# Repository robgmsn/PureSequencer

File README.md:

DESIGN STATUS: Production

Sequencer Updated to V2.31 28/4/21

Power Supply updated pull 5V from main case power supply, in line with low noise techniques.
Some resistor values reduced to 10k, in line with low noise techniques.
Traces rerouted.

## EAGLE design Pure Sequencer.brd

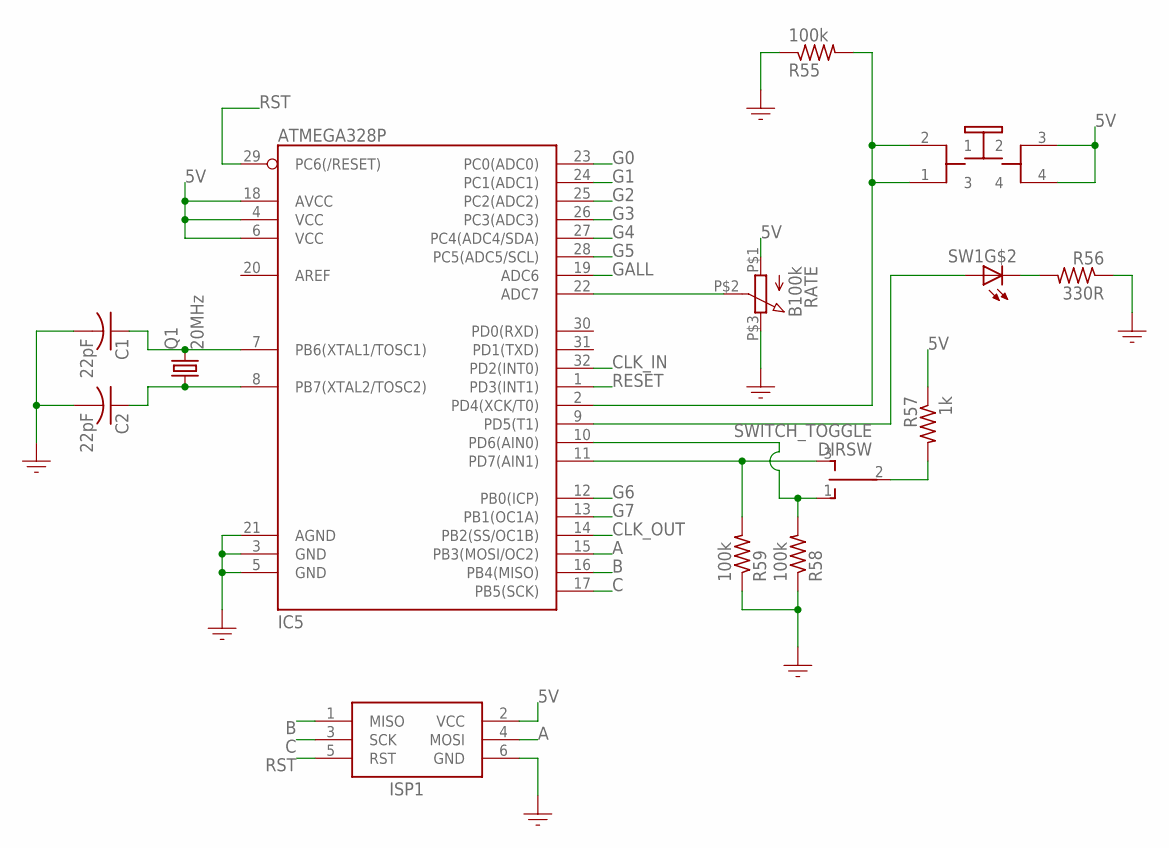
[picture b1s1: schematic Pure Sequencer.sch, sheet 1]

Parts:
C1, C2: 22pF; C0805
DIRSW: SWITCH_TOGGLE; TOGGLE_SW
IC5: ATMEGA328P; TQFP32-08
ISP1: HEADER2X3-6; AVRISP
Q1: 20MHz; HC49UP
R55, R58, R59: 100k; R0805
R56: 330R; R0805
R57: 1k; R0805
RATE: B100k; POTENTIOMETER_9MM
SW1: SWITCH_PUSHBUTTON_LED; PB6149L

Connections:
5V: IC5.4 (VCC), IC5.6 (VCC), IC5.18 (AVCC), ISP1.2 (VCC), R57.1, RATE.P$1 (1), SW1.3 (2), SW1.4; also elsewhere on the board
A: IC5.15 (PB3(MOSI/OC2)), ISP1.4 (MOSI); also elsewhere on the board
B: IC5.16 (PB4(MISO)), ISP1.1 (MISO); also elsewhere on the board
C: IC5.17 (PB5(SCK)), ISP1.3 (SCK); also elsewhere on the board
CLK_IN: IC5.32 (PD2(INT0)); also elsewhere on the board
CLK_OUT: IC5.14 (PB2(SS/OC1B)); also elsewhere on the board
G0: IC5.23 (PC0(ADC0)); also elsewhere on the board
G1: IC5.24 (PC1(ADC1)); also elsewhere on the board
G2: IC5.25 (PC2(ADC2)); also elsewhere on the board
G3: IC5.26 (PC3(ADC3)); also elsewhere on the board
G4: IC5.27 (PC4(ADC4/SDA)); also elsewhere on the board
G5: IC5.28 (PC5(ADC5/SCL)); also elsewhere on the board
G6: IC5.12 (PB0(ICP)); also elsewhere on the board
G7: IC5.13 (PB1(OC1A)); also elsewhere on the board
GALL: IC5.19 (ADC6)
GND: C1.2, C2.2, IC5.3 (GND), IC5.5 (GND), IC5.21 (AGND), ISP1.6 (GND), R55.1, R56.1, R58.1, R59.1, RATE.P$3 (3); also elsewhere on the board
unnamed: C1.1, IC5.7 (PB6(XTAL1/TOSC1)), Q1.2
unnamed: C2.1, IC5.8 (PB7(XTAL2/TOSC2)), Q1.1
unnamed: IC5.22 (ADC7), RATE.P$2 (2)
unnamed: IC5.2 (PD4(XCK/T0)), R55.2, SW1.1 (3), SW1.2 (1)
unnamed: IC5.9 (PD5(T1)), SW1.A
unnamed: R56.2, SW1.K (C)
unnamed: DIRSW.2, R57.2
unnamed: DIRSW.1 (O), IC5.10 (PD6(AIN0)), R58.2
unnamed: DIRSW.3 (S), IC5.11 (PD7(AIN1)), R59.2
RESET: IC5.1 (PD3(INT1)); also elsewhere on the board
RST: IC5.29 (PC6(/RESET)), ISP1.5 (RST)

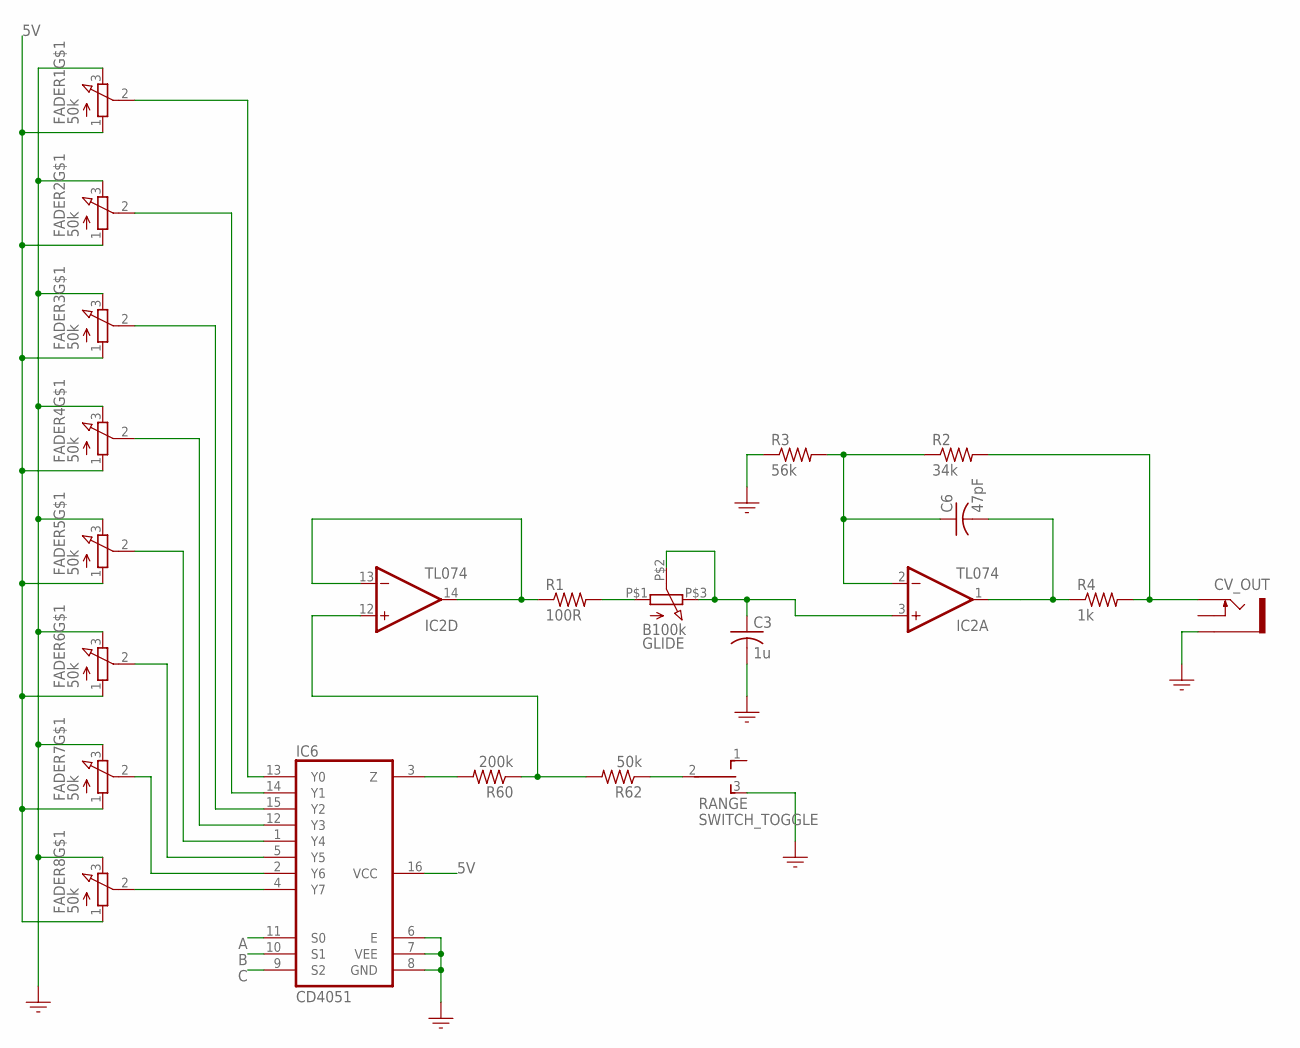
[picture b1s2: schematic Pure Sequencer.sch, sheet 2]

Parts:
C3: 1u; C0805
C6: 47pF; C0805
CV_OUT: PJ301M-12
FADER1, FADER2, FADER3, FADER4, FADER5, FADER6, FADER7, FADER8: 50k; FADER_20MM_LED
GLIDE: B100k; POTENTIOMETER_9MM
IC2: TL074; SO14
IC6: CD4051; SOIC_16
R1: 100R; R0805
R2: 34k; R0805
R3: 56k; R0805
R4: 1k; R0805
R60: 200k; R0805
R62: 50k; R0805
RANGE: SWITCH_TOGGLE; TOGGLE_SW

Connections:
5V: FADER1.1, FADER2.1, FADER3.1, FADER4.1, FADER5.1, FADER6.1, FADER7.1, FADER8.1, IC6.16 (VCC); also elsewhere on the board
A: IC6.11 (S0); also elsewhere on the board
B: IC6.10 (S1); also elsewhere on the board
C: IC6.9 (S2); also elsewhere on the board
GND: C3.2, CV_OUT.GND (SLEEVE), FADER1.3, FADER2.3, FADER3.3, FADER4.3, FADER5.3, FADER6.3, FADER7.3, FADER8.3, IC6.6 (E), IC6.7 (VEE), IC6.8 (GND), R3.1, RANGE.3 (S); also elsewhere on the board
unnamed: IC2.12 (+IN), R60.1, R62.2
unnamed: IC2.13 (-IN), IC2.14 (OUT), R1.1
unnamed: GLIDE.P$1 (1), R1.2
unnamed: FADER8.2, IC6.4 (Y7)
unnamed: FADER7.2, IC6.2 (Y6)
unnamed: FADER6.2, IC6.5 (Y5)
unnamed: FADER5.2, IC6.1 (Y4)
unnamed: FADER4.2, IC6.12 (Y3)
unnamed: FADER3.2, IC6.15 (Y2)
unnamed: FADER2.2, IC6.14 (Y1)
unnamed: FADER1.2, IC6.13 (Y0)
unnamed: C3.1, GLIDE.P$2 (2), GLIDE.P$3 (3), IC2.3 (+IN)
unnamed: C6.1, IC2.2 (-IN), R2.1, R3.2
unnamed: C6.2, IC2.1 (OUT), R4.1
unnamed: CV_OUT.TIP, R2.2, R4.2
unnamed: IC6.3 (Z), R60.2
unnamed: R62.1, RANGE.2

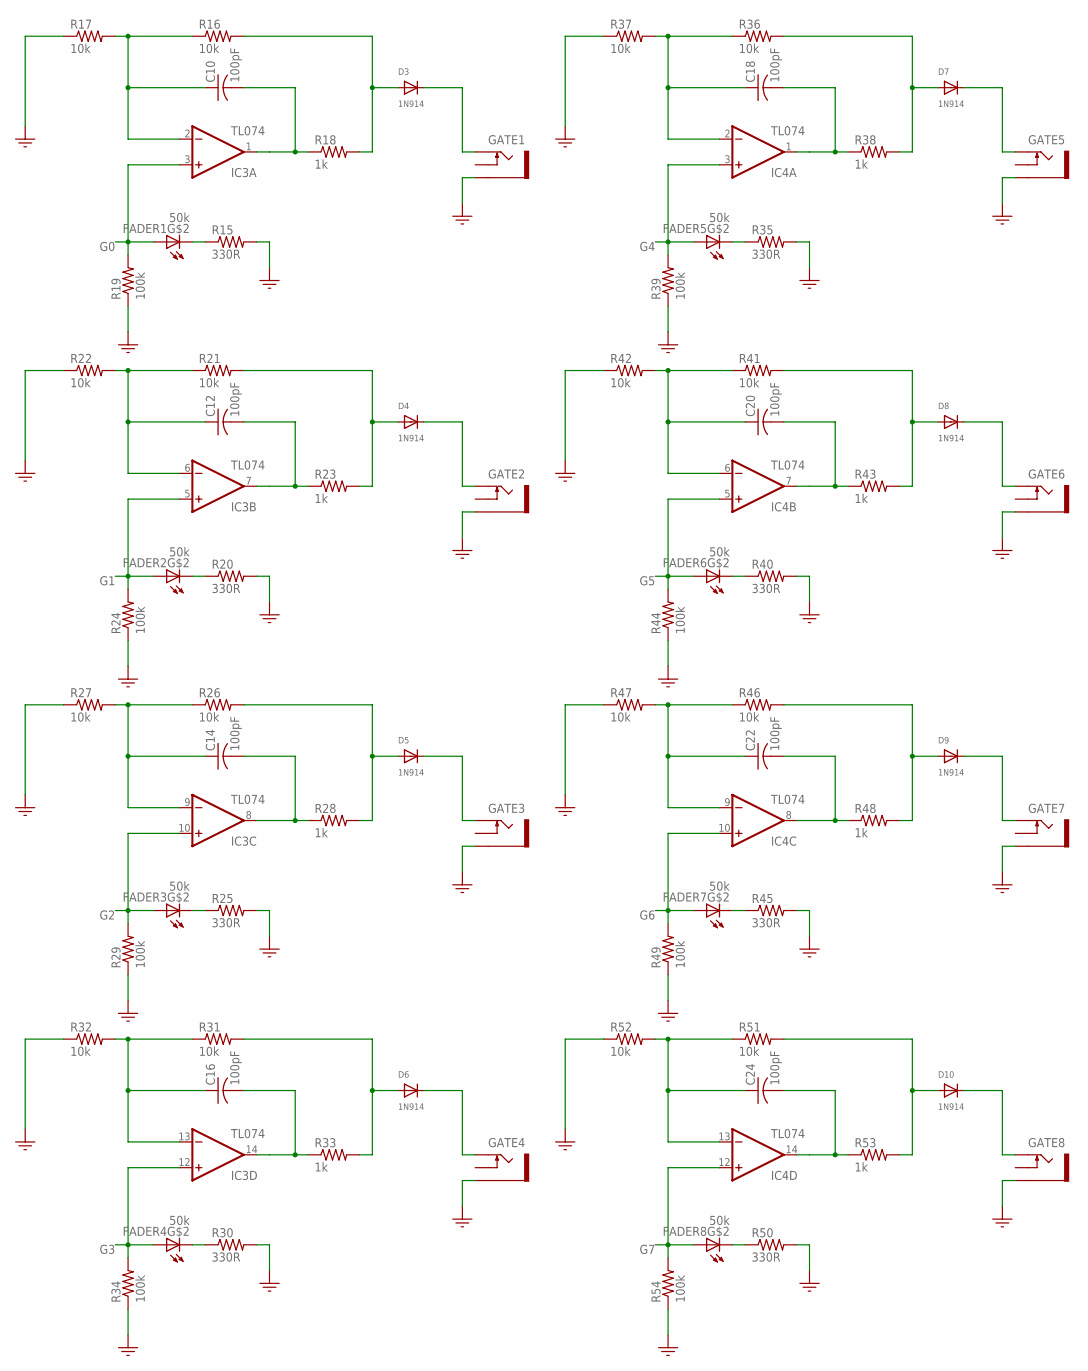
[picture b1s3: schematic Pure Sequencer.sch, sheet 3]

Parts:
C10, C12, C14, C16, C18, C20, C22, C24: 100pF; C0805
D3, D4, D5, D6, D7, D8, D9, D10: 1N914; DO-41
FADER1, FADER2, FADER3, FADER4, FADER5, FADER6, FADER7, FADER8: 50k; FADER_20MM_LED
GATE1, GATE2, GATE3, GATE4, GATE5, GATE6, GATE7, GATE8: PJ301M-12
IC3, IC4: TL074; SO14
R15, R20, R25, R30, R35, R40, R45, R50: 330R; R0805
R16, R17, R21, R22, R26, R27, R31, R32, R36, R37, R41, R42, R46, R47, R51, R52: 10k; R0805
R18, R23, R28, R33, R38, R43, R48, R53: 1k; R0805
R19, R24, R29, R34, R39, R44, R49, R54: 100k; R0805

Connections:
G0: FADER1.A, IC3.3 (+IN), R19.2; also elsewhere on the board
G1: FADER2.A, IC3.5 (+IN), R24.2; also elsewhere on the board
G2: FADER3.A, IC3.10 (+IN), R29.2; also elsewhere on the board
G3: FADER4.A, IC3.12 (+IN), R34.2; also elsewhere on the board
G4: FADER5.A, IC4.3 (+IN), R39.2; also elsewhere on the board
G5: FADER6.A, IC4.5 (+IN), R44.2; also elsewhere on the board
G6: FADER7.A, IC4.10 (+IN), R49.2; also elsewhere on the board
G7: FADER8.A, IC4.12 (+IN), R54.2; also elsewhere on the board
GND: GATE1.GND (SLEEVE), GATE2.GND (SLEEVE), GATE3.GND (SLEEVE), GATE4.GND (SLEEVE), GATE5.GND (SLEEVE), GATE6.GND (SLEEVE), GATE7.GND (SLEEVE), GATE8.GND (SLEEVE), R15.2, R17.1, R19.1, R20.2, R22.1, R24.1, R25.2, R27.1, R29.1, R30.2, R32.1, R34.1, R35.2, R37.1, R39.1, R40.2, R42.1, R44.1, R45.2, R47.1, R49.1, R50.2, R52.1, R54.1; also elsewhere on the board
unnamed: FADER1.K (C), R15.1
unnamed: C10.1, IC3.2 (-IN), R16.1, R17.2
unnamed: C10.2, IC3.1 (OUT), R18.1
unnamed: D3.A, R16.2, R18.2
unnamed: FADER3.K (C), R25.1
unnamed: FADER2.K (C), R20.1
unnamed: C12.1, IC3.6 (-IN), R21.1, R22.2
unnamed: C12.2, IC3.7 (OUT), R23.1
unnamed: D4.A, R21.2, R23.2
unnamed: C14.1, IC3.9 (-IN), R26.1, R27.2
unnamed: C14.2, IC3.8 (OUT), R28.1
unnamed: D5.A, R26.2, R28.2
unnamed: FADER4.K (C), R30.1
unnamed: C16.1, IC3.13 (-IN), R31.1, R32.2
unnamed: C16.2, IC3.14 (OUT), R33.1
unnamed: D6.A, R31.2, R33.2
unnamed: FADER5.K (C), R35.1
unnamed: C18.1, IC4.2 (-IN), R36.1, R37.2
unnamed: C18.2, IC4.1 (OUT), R38.1
unnamed: D7.A, R36.2, R38.2
unnamed: FADER6.K (C), R40.1
unnamed: C20.1, IC4.6 (-IN), R41.1, R42.2
unnamed: C20.2, IC4.7 (OUT), R43.1
unnamed: D8.A, R41.2, R43.2
unnamed: FADER7.K (C), R45.1
unnamed: C22.1, IC4.9 (-IN), R46.1, R47.2
unnamed: C22.2, IC4.8 (OUT), R48.1
unnamed: D9.A, R46.2, R48.2
unnamed: FADER8.K (C), R50.1
unnamed: C24.1, IC4.13 (-IN), R51.1, R52.2
unnamed: C24.2, IC4.14 (OUT), R53.1
unnamed: D10.A, R51.2, R53.2
unnamed: D6.C, GATE4.TIP
unnamed: D5.C, GATE3.TIP
unnamed: D4.C, GATE2.TIP
unnamed: D3.C, GATE1.TIP
unnamed: D10.C, GATE8.TIP
unnamed: D9.C, GATE7.TIP
unnamed: D8.C, GATE6.TIP
unnamed: D7.C, GATE5.TIP

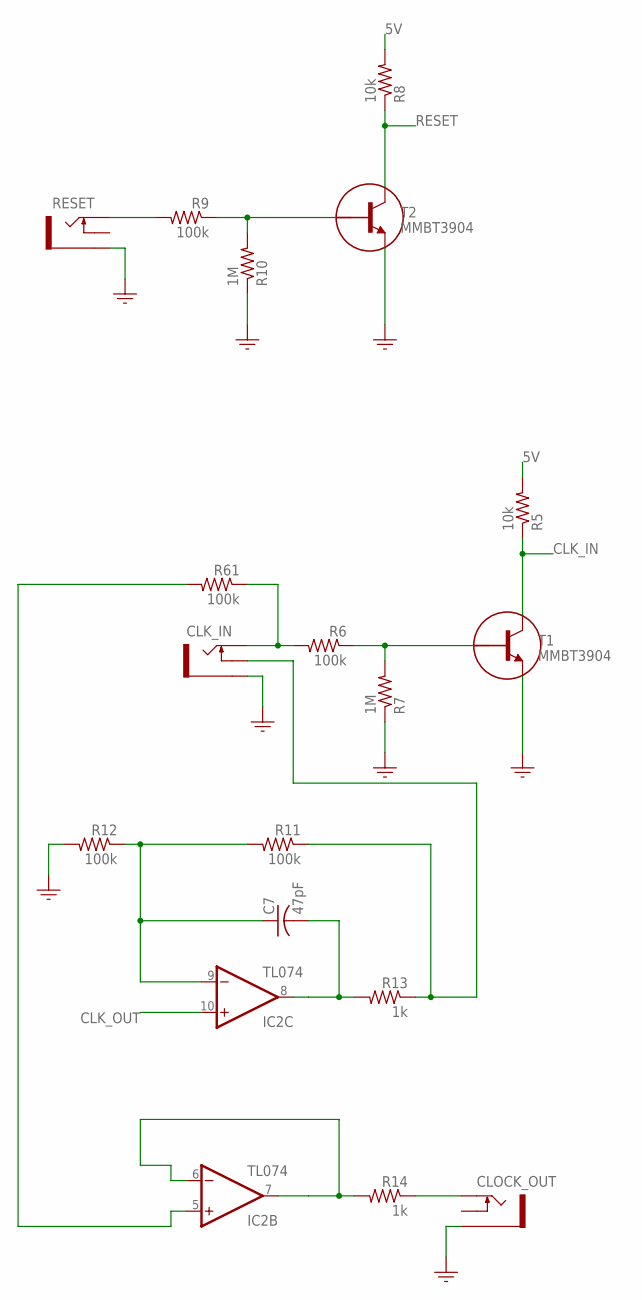
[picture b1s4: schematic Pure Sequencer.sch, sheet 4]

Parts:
C7: 47pF; C0805
CLK_IN: PJ301M-12
CLOCK_OUT: PJ301M-12
IC2: TL074; SO14
R5, R8: 10k; R0805
R6, R9, R11, R12, R61: 100k; R0805
R7, R10: 1M; R0805
R13, R14: 1k; R0805
RESET: PJ301M-12
T1, T2: MMBT3904; SOT23

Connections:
5V: R5.2, R8.2; also elsewhere on the board
CLK_IN: R5.1, T1.3 (C); also elsewhere on the board
CLK_OUT: IC2.10 (+IN); also elsewhere on the board
GND: CLK_IN.GND (SLEEVE), CLOCK_OUT.GND (SLEEVE), R7.1, R10.1, R12.2, RESET.GND (SLEEVE), T1.2 (E), T2.2 (E); also elsewhere on the board
unnamed: R6.1, R7.2, T1.1 (B)
unnamed: IC2.5 (+IN), R61.2
unnamed: R9.1, R10.2, T2.1 (B)
unnamed: R9.2, RESET.TIP
unnamed: C7.1, IC2.9 (-IN), R11.2, R12.1
unnamed: C7.2, IC2.8 (OUT), R13.2
unnamed: CLK_IN.TIP, R6.2, R61.1
unnamed: IC2.6 (-IN), IC2.7 (OUT), R14.2
unnamed: CLOCK_OUT.TIP, R14.1
unnamed: CLK_IN.NORM (SWITCH), R11.1, R13.1
RESET: R8.1, T2.3 (C); also elsewhere on the board

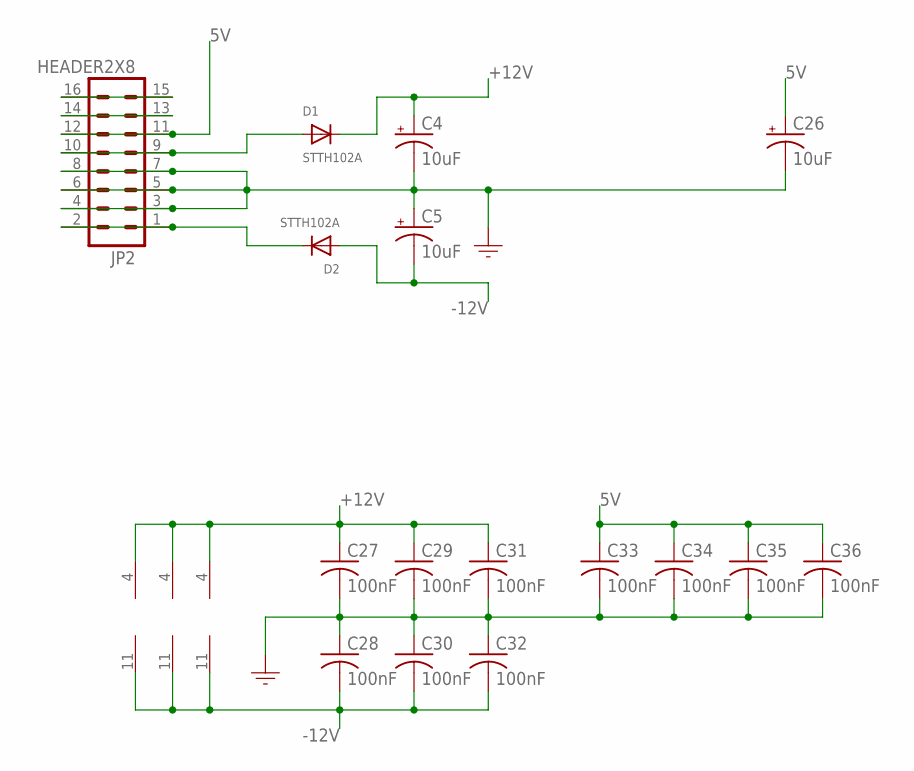
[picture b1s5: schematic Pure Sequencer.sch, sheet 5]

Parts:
C4, C5, C26: 10uF; 153CLV-0505
C27, C28, C29, C30, C31, C32, C33, C34, C35, C36: 100nF; C0805
D1, D2: STTH102A; SMADIODE
IC2, IC3, IC4: TL074; SO14
JP2: HEADER2X8; POWER_SHROUDED

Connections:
5V: C26.+, C33.1, C34.1, C35.1, C36.1, JP2.11, JP2.12; also elsewhere on the board
+12V: C4.+, C27.1, C29.1, C31.1, D1.C, IC2.4 (V+), IC3.4 (V+), IC4.4 (V+)
-12V: C5.-, C28.2, C30.2, C32.2, D2.A, IC2.11 (V-), IC3.11 (V-), IC4.11 (V-)
GND: C4.-, C5.+, C26.-, C27.2, C28.1, C29.2, C30.1, C31.2, C32.1, C33.2, C34.2, C35.2, C36.2, JP2.3, JP2.4, JP2.5, JP2.6, JP2.7, JP2.8; also elsewhere on the board
unnamed: D1.A, JP2.9, JP2.10
unnamed: D2.C, JP2.1, JP2.2
unnamed: JP2.13, JP2.14
unnamed: JP2.15, JP2.16

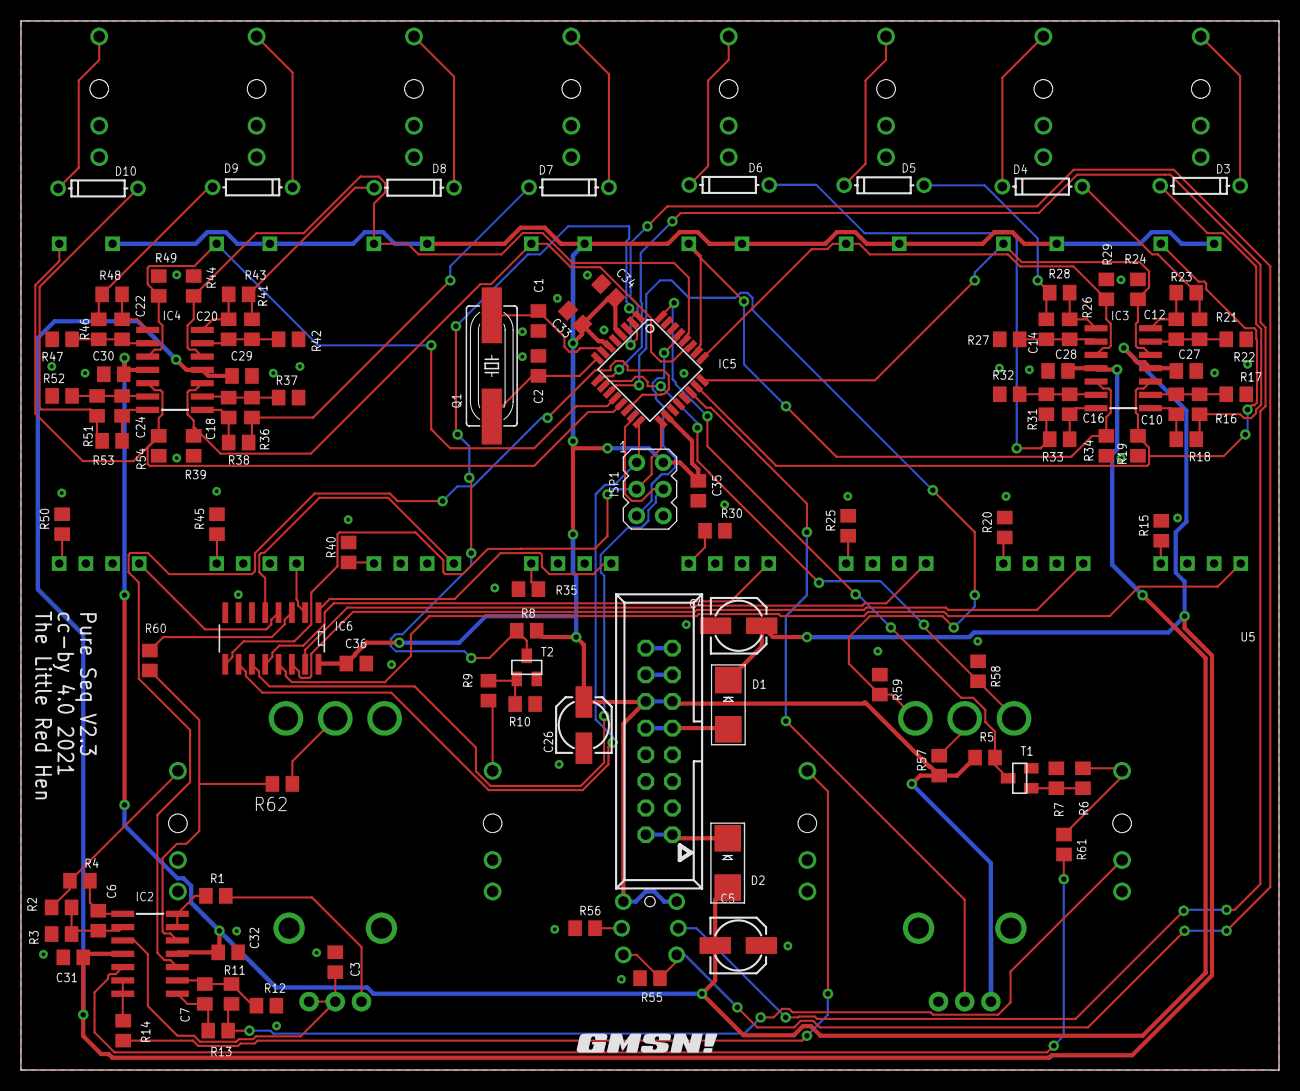
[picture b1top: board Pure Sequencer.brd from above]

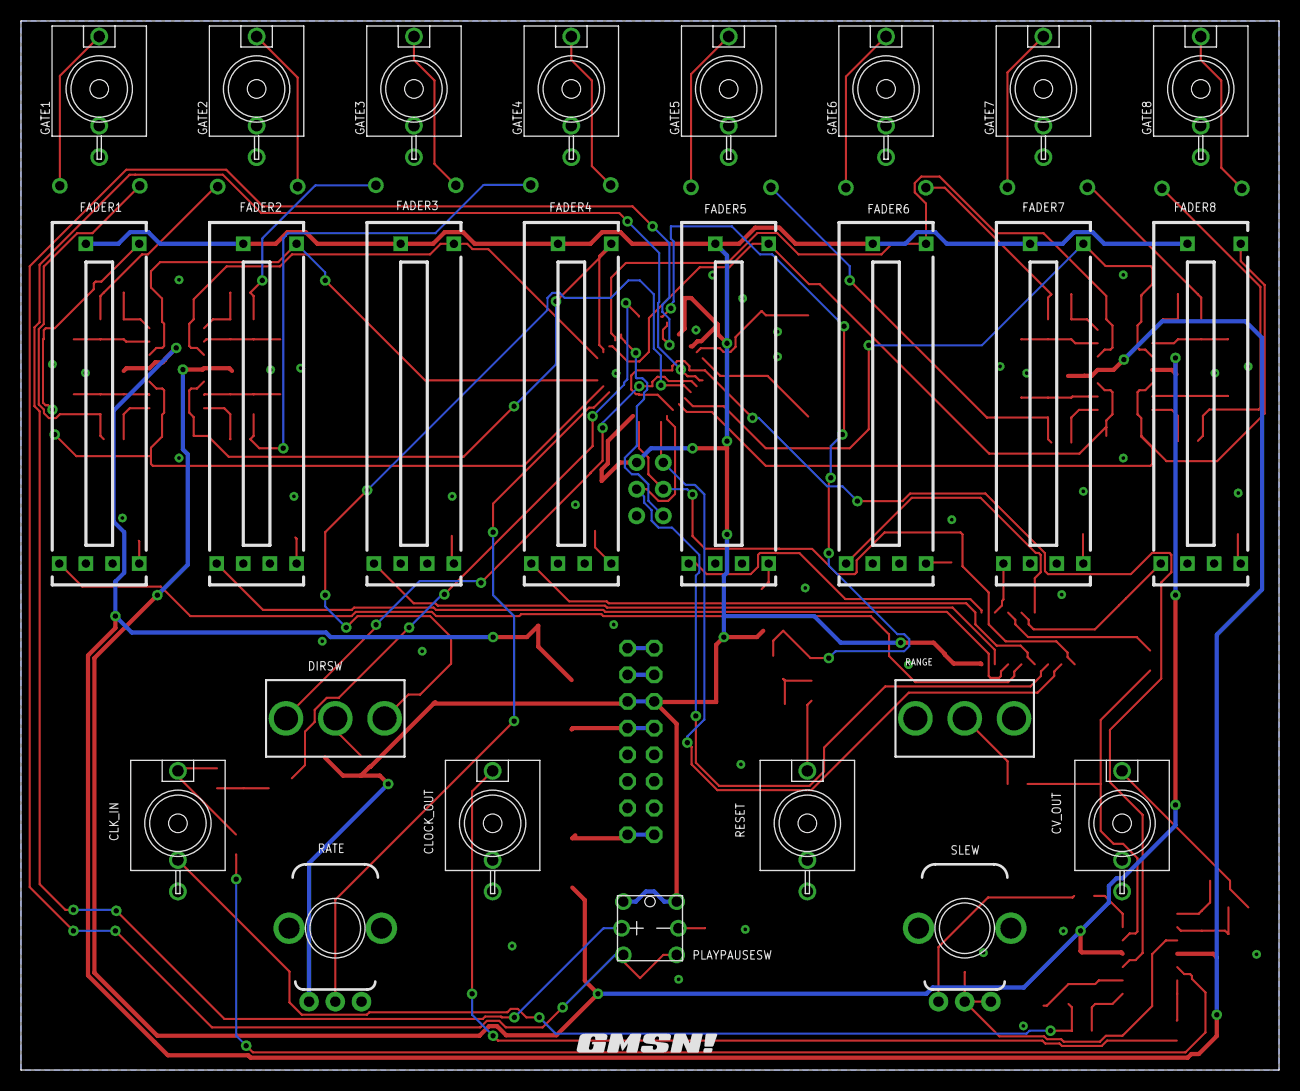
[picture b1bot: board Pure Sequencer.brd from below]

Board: 2 copper layers, 119.9 x 100.0 mm, 135 parts (26 on the bottom side), 99 nets.

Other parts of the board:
U$1, U$2: GMSN!_LOGO

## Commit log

2021-04-16 Sequencer 2.1
2021-04-16 Sequencer 2.2
2021-04-16 Backlink to CADLAB.io has been added.
2021-04-16 Sequencer 2.21
    Code added to repo
2021-04-20 Sequencer 2.3
    Sequencer Updated to V2.3 20/4/21
    Power Supply updated pull 5V from main case power supply, in line with low noise techniques.
    Some resistor values reduced to 10k, in line with low noise techniques.
    Traces rerouted.
2021-04-25 Sequencer 2.21
    Code moved to folder as per Arduino IDE requirements.
2021-04-28 Sequencer 2.31
    Sequencer Updated to V2.31 28/4/21
    Power Supply updated pull 5V from main case power supply, in line with low noise techniques.
    Some resistor values reduced to 10k, in line with low noise techniques.
    Traces rerouted.
2021-07-07 Reinstall

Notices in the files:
Pure Sequencer.brd:
cc-by 4.0 2021
